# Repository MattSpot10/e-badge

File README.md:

# eBadge

**eBadge** is a customizable, hackable electronics badge designed for students to explore, build, and learn throughout their academic journey. It’s more than just a badge—it's a personal electronics lab, wearable project canvas, and long-term learning tool.

## Features

- Custom PCB with microcontroller 
- Modular peripherals: LEDs, sensors, buttons, displays, etc.
- Fully programmable with open-source firmware
- Designed for learning — from blinking LEDs to building full apps
- Battery-powered & portable — perfect for hacking on the go

## What’s in This Repo?

```bash
e-badge/
├── docs/           # Project documentation, setup guides, and images
├── hardware/       # Schematics, PCB layouts, BOMs, and 3D models
├── firmware/       # Embedded code for the badge's microcontroller
├── software/       # Host-side apps, test tools, or configurators
├── assets/         # Logos, badge graphics, and artwork
├── test/           # Scripts for testing hardware and firmware
├── LICENSE-CODE
├── LICENSE-HARDWARE
├── LICENSE-DOCS
├── README.md
└── .gitignore
```
## License

- **Hardware** – [CERN-OHL-S v2.0](./LICENSE-HARDWARE)
- **Firmware/Code** – [MIT License](./LICENSE-CODE)
- **Docs & Assets** – [CC BY-SA 4.0](./LICENSE-DOCS)

## Contributors

- Nathan Jack (jackn@byui.edu)
- Lynn Watson (watsonl@byui.edu)
- Jason Allred (allredjas@byui.edu)
- Richard Grimmett (grimmettr@byui.edu)
- Carl Gibbons (gibbonsc@byui.edu)
- Craig Lindstrom (lindstromc@byui.edu)
- Gary Godderidge (godderidgeg@byui.edu)
- Matt Manley (manleym@byui.edu)

# TODO (Senior project, delete when done)
- Fix screen connector
	- Use LCSC part C11086

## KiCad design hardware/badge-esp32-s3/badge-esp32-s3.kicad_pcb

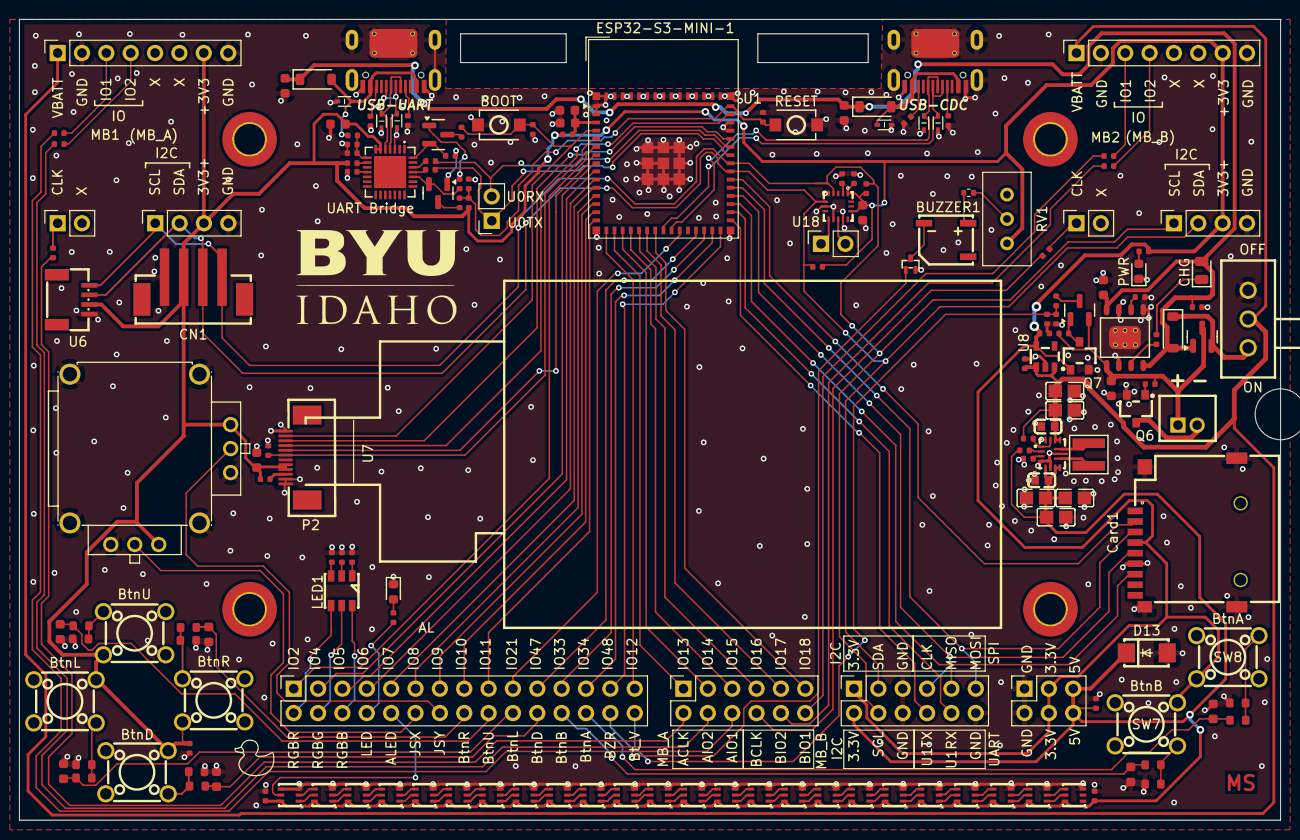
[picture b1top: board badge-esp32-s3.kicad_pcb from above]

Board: 2 copper layers, 131.5 x 83.5 mm, 180 parts (0 on the bottom side), 169 nets.

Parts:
AL1, AL2, AL3, AL4, AL5, AL6, AL7, AL8, AL9, AL10, AL11, AL12, AL13, AL14, AL15, AL16, AL17, AL18, AL19, AL20, AL21, AL22, AL23, AL24: LED-SMD_6P-L2.2-W2.2-TL-1
BUZZER1: MLT-5020; BUZ-SMD_L5.0-W5.5-P4.60
C1, C5, C6, C7, C12, C13: 10uF; C_0603
C2, C14: 100nF; C_0603
C3, C4, C8, C9, C15, C16, C32, C33: 1uF; C_0402
C10, C11, C25, C34, C35, C36: 100nF; C_0402
C17, C27: 10uF; C0805
C18, C19, C20, C21, C22, C23: 1uF; C_0603
C26: 4.7uF; C_0603
C28, C37: TMK107BBJ106MA-T; C0603
C29, C30, C31: 22uF; C0805
CN1: B4B-PH-SM4-TB (LF)(SN); CONN-SMD_B4B-PH-SM4-TB-LF-SN
Card1: TF PUSH; TF-SMD_TF-PUSH
D1, D14: Red; D_0603
D2, D3, D4, D6, D7, D8: LESD5D5.0CT1G; SOD-523_L1.2-W0.8-LS1.6-BI
D5, D9, D11: B0520W; D_SOD-123
D12: Green; D_0805
D13: SMAJ7.0A; SMA_L4.5-W2.6-LS5.1-RD
H1, H2, H3, H4: MountingHole; MountingHole_3.2mm_M3_ISO7380_Pad_TopBottom
H5: MountingHole; MountingHole_5.3mm_M5
J1, J2: Connector, USB-TYPE-C-16P; TYPE-C-SMD_HX-TYPE-C-16PIN
J3, J9: Conn_02x06_Odd_Even; PinSocket_2x06_P2.54mm_Vertical
J4: Conn_02x15_Odd_Even; PinSocket_2x15_P2.54mm_Vertical
J5, J12, J14, J15: Conn_01x02_Socket; PinSocket_1x02_P2.54mm_Vertical
J6, J13: Conn_01x04_Socket; PinSocket_1x04_P2.54mm_Vertical
J7, J8: Conn_01x08_Socket; PinSocket_1x08_P2.54mm_Vertical
J11: Conn_02x03_Odd_Even; PinSocket_2x03_P2.54mm_Vertical
L3: XGL4020-152MEC; IND-SMD_L4.0-W4.0_XEL4020
LED1: RS-3535MWAM; LED-ARRAY-SMD_L3.7-W3.5-P1.10-TL
MB1, MB2: MiniBadge_Full; MiniBadge_Full_NoEdges
P1: PH-2A_C2319; CONN-TH_2P-P2.00_PH-2A_C2319
P2: FPC 0.5MM 12P Pull type H2.0mm Pick up; FPC-SMD_12P-L11.5-W5.4-P0.50
Power1: SK-12F04-G050; SW-TH_G-SWITCH_SK-12F04-G050
Q1, Q2: SS8050 200-350; Q_SOT-23
Q3, Q4: HL2301A; Q_SOT-23
Q5: DTC114E; DTC114EE
Q6, Q7: AO3424; SC-59-3_L2.9-W1.6-P0.95-LS2.9-BR
R1, R11, R12: 0Ω; R_0402
R2, R3, R4, R5, R6, R19: 5.1kΩ; R_0402
R7: 22kΩ; R_0402
R8, R46: 47kΩ; R_0402
R9, R25: 1kΩ; R_0402
R10, R13, R14, R17, R54: 10kΩ; R_0402
R15, R16: 470Ω; R_0402
R18, R20, R40, R47, R49, R50, R51, R52: 100Ω; R_0402
R21, R22: 47Ω; R_0402
R23: YF16-FL7.2-B5KA(45-10)-R-A28; JOYTICK-TH_YF16-DFL7.2-B5KO-45-10-B5KO-55--RG-A22
R24, R39, R44, R48, R53: 100kΩ; R_0402
R26: 2.2kΩ; R_0402
R27, R28, R29, R30, R31, R32, R33, R34, R35, R36, R37, R38: 10kΩ; R_0603
R41: 150kΩ; R_0402
R42: 27Ω; R_0402_1005Metric
R43, R45: 4.7kΩ; R_0402
RV1: 1000Ω; Potentiometer_Bourns_3296W_Vertical
SW1, SW2: TS-1088-AR02016; SW-SMD_L3.9-W3.0-P4.45
SW4, SW5, SW6, SW7, SW8, SW9: TS665CJ; SW-TH_4P-L6.0-W6.0-P4.50-LS6.5
U1: ESP32-S3-MINI-1-N4R2; ESP32-S2-MINI-1
U2: TPS630701RNMR; VQFN-HR-15_L3.0-W2.5-P0.50-BL_TPS63070RNMR
U3: CP2102N-A02-GQFN28R; QFN-28_L5.0-W5.0-P0.50-TL-EP3.3
U4: TP4056; ESOP-8_L4.9-W3.9-P1.27-LS6.0-BL-EP
U6: ZX-SH1.0-4PWT; CONN-SMD_4P-P1.00_MEGASTAR_ZX-SH1.0-4PWT
U7: HS20HS072RX-fpc; OLED-SMD_HS20HS072RX-pins_removed
U8: TLV75733PDBVR; SOT-23-5_L2.9-W1.6-P0.95-LS2.8-BL
U18: MMA8452QR1_C11360; QFN-16_L3.0-W3.0-P0.50-TL_MMA8452QR1

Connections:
+3.3V: C4.1, C7.1, C10.1, C14.1, C16.1, C26.2, CN1.3, Card1.4 (VDD), J3.1, J6.3, J7.7, J8.7, J11.3, J11.4, J13.3, P2.8 (IOVCC), P2.9 (VCC), Q7.1 (G), R1.2, R2.1, R9.2, R17.1, R18.1, R23.3, R23.4, R43.1, R45.1, RV1.1, SW4.2 (B), SW5.2 (B), SW6.2 (B), SW7.2 (B), SW8.2 (B), SW9.2 (B), U3.6 (VDD), U3.7 (VREGIN), U6.3, U8.5 (OUT), U18.1 (VDDIO), U18.14 (VDD)
/5V_stable: AL1.3 (VDD), AL2.3 (VDD), AL3.3 (VDD), AL4.3 (VDD), AL5.3 (VDD), AL6.3 (VDD), AL7.3 (VDD), AL8.3 (VDD), AL9.3 (VDD), AL10.3 (VDD), AL11.3 (VDD), AL12.3 (VDD), AL13.3 (VDD), AL14.3 (VDD), AL15.3 (VDD), AL16.3 (VDD), AL17.3 (VDD), AL18.3 (VDD), AL19.3 (VDD), AL20.3 (VDD), AL21.3 (VDD), AL22.3 (VDD), AL23.3 (VDD), AL24.3 (VDD), C15.1, C29.2, C30.2, C31.2, C32.1, C33.1, C37.2, D13.1 (K), J3.2, J11.5, J11.6, R53.1, U2.5 (FB), U2.7 (VOUT), U2.8 (VOUT)
/AButtonMid: C22.1, J4.26, R36.2
/AddrLedMid: AL1.2 (DI), J4.10
/BButtonMid: C21.1, J4.24, R34.2
/BatteryVoltage: C34.1, J4.30, R41.2, R46.1
/BuzzerMid: J4.28, Q5.1 (B)
/DownButtonMid: C23.1, J4.22, R38.2
/ESP_EN: C9.1, C36.2, R15.2, R17.2, SW2.2, U1.45 (EN)
/ESP_USB+: D6.2, J2.A6 (D+), J2.B6 (D+), U1.24 (USB_D+)
/ESP_USB-: D7.2, J2.A7 (D-), J2.B7 (D-), U1.23 (USB_D-)
/GPIO0: C35.2, P2.2 (CS), R16.2, SW1.2, U1.4 (IO0)
/GPIO1: P2.6 (RST), R39.1, U1.5 (IO1)
/GPIO2: J4.1, U1.6 (IO2)
/GPIO3: P2.5 (SDA), U1.7 (IO3)
/GPIO4: J4.3, U1.8 (IO4)
/GPIO5: J4.5, U1.9 (IO5)
/GPIO6: J4.7, U1.10 (IO6)
/GPIO7: J4.9, U1.11 (IO7)
/GPIO8: J4.11, U1.12 (IO8)
/GPIO9: J4.13, U1.13 (IO9)
/GPIO10: J4.15, U1.14 (IO10)
/GPIO11: J4.17, U1.15 (IO11)
/GPIO12: J4.29, U1.16 (IO12)
/GPIO13: J9.1, U1.17 (IO13)
/GPIO14: J9.3, U1.18 (IO14)
/GPIO15: J9.5, U1.19 (IO15)
/GPIO16: J9.7, U1.20 (IO16)
/GPIO17: J9.9, U1.21 (IO17)
/GPIO18: J9.11, U1.22 (IO18)
/GPIO21: J4.19, U1.25 (IO21)
/GPIO33: J4.23, U1.28 (IO33)
/GPIO34: J4.25, U1.29 (IO34)
/GPIO35: J3.8, U1.31 (IO35)
/GPIO36: J3.10, U1.32 (IO36)
/GPIO37: Card1.7 (DAT0), J3.9, U1.33 (IO37)
/GPIO38: Card1.5 (CLX), J3.7, U1.34 (IO38)
/GPIO39: Card1.3 (CMD), J3.11, U1.35 (IO39)
/GPIO40: Card1.2 (CD/DAT3), U1.36 (IO40)
/GPIO41: CN1.2, J3.3, J6.2, J13.2, R45.2, U1.37 (IO41), U6.2, U18.6 (SDA)
/GPIO42: CN1.1, J3.4, J6.1, J13.1, R43.2, U1.38 (IO42), U6.1, U18.4 (SCL)
/GPIO45: P2.3 (RS), U1.41 (IO45)
/GPIO46: P2.4 (SCL), U1.44 (IO46)
/GPIO47: J4.21, U1.27 (IO47)
/GPIO48: J4.27, U1.30 (IO48)
/JoystickXMid: J4.12, R23.2
/JoystickYMid: J4.14, R23.5
/LEDSingleMid: J4.8, R19.1
/LEDs/BO_AL9: AL9.5 (BO), AL10.1 (BI)
/LEDs/BO_AL18: AL18.5 (BO), AL19.1 (BI)
/LEDs/DO_AL9: AL9.4 (DO), AL10.2 (DI)
/LEDs/DO_AL18: AL18.4 (DO), AL19.2 (DI)
/LeftButtonMid: C18.1, J4.20, R28.2
/Onboard Peripheral/Accelormeter/INT 1 (output to MCU, NN): J15.2, U18.11 (INT1)
/Onboard Peripheral/Accelormeter/INT 2 (output to MCU, NN): J15.1, U18.9 (INT2)
/RGBBlueMid: J4.6, LED1.6 (+)
/RGBGreenMid: J4.4, LED1.5 (+)
/RGBRedMid: J4.2, LED1.4 (+)
/RightButtonMid: C20.1, J4.16, R32.2
/U0RX: J14.2, R11.2, U1.40 (RXD0)
/U0TX: J14.1, R12.2, U1.39 (TXD0)
/UART Interface/USB_DN: D3.2, J1.A7 (D-), J1.B7 (D-), U3.5 (D-)
/UART Interface/USB_DP: D2.2, J1.A6 (D+), J1.B6 (D+), U3.4 (D+)
/USB_5V: C5.1, C6.1, C12.1, D5.1, D9.1, D11.2, D12.2, Q3.1 (G), R24.2, U4.4 (VCC), U4.8 (CE)
/UpButtonMid: C19.1, J4.18, R30.2
/VBATT: C13.1, P1.1, Q3.3 (D), Q4.2 (S), R44.1, R48.2, U4.5 (BAT)
/VBUS: D4.2, D5.2, J1.A9B4 (VBUS), J1.B9A4 (VBUS), R7.1
/VBUSB: D8.2, D9.2, J2.A9B4 (VBUS), J2.B9A4 (VBUS)
/minibadge/MB1CLK: J9.2, R49.2
/minibadge/MB1IO1: J9.6, R40.1
/minibadge/MB1IO2: J9.4, R47.1
/minibadge/MB2CLK: J9.8, R52.2
/minibadge/MB2IO1: J9.12, R50.1
/minibadge/MB2IO2: J9.10, R51.1
GND: AL1.1 (BI), AL1.6 (GND), AL2.6 (GND), AL3.6 (GND), AL4.6 (GND), AL5.6 (GND), AL6.6 (GND), AL7.6 (GND), AL8.6 (GND), AL9.6 (GND), AL10.6 (GND), AL11.6 (GND), AL12.6 (GND), AL13.6 (GND), AL14.6 (GND), AL15.6 (GND), AL16.6 (GND), AL17.6 (GND), AL18.6 (GND), AL19.6 (GND), AL20.6 (GND), AL21.6 (GND), AL22.6 (GND), AL23.6 (GND), AL24.6 (GND), C1.2, C2.2, C3.2, C4.2, C5.2, C6.2, C7.2, C8.2, C9.2, C10.2, C11.2, C12.2, C13.2, C14.2, C15.2, C16.2, C17.1, C18.2, C19.2, C20.2, C21.2, C22.2, C23.2, C25.2, C26.1, C27.1, C28.1, C29.1, C30.1, C31.1, C32.2, C33.2, C34.2, C35.1, C36.1, C37.1, CN1.4, Card1.6 (VSS), Card1.10, Card1.11, Card1.12, Card1.13, D1.1, D2.1, D3.1, D4.1, D6.1, D7.1, D8.1, D13.2 (A), D14.1, J1.A12B1 (GND), J1.B12A1 (GND), J1.S1 (SHIELD), J2.A12B1 (GND), J2.B12A1 (GND), J2.S1 (SHIELD), J3.5, J3.6, J3.12, J6.4, J7.2, J7.8, J8.2, J8.8, J11.1, J11.2, J13.4, P2.1 (GND), P2.11 (K), P2.12 (GND), Power1.3, Q5.2 (E), Q6.2 (S), Q7.2 (S), R3.2, R4.2, R5.2, R6.2, R8.2, R10.2, R20.2, R21.2, R22.2, R23.1, R23.6, R23.7 (shell), R23.8 (shell), R23.9 (shell), R23.10 (shell), R24.1, R26.2, R27.2, R29.2, R31.2, R33.2, R35.2, R37.2, R39.2, R46.2, SW1.1, SW2.1, U1.1 (GND), U1.2 (GND), U1.42 (GND), U1.43 (GND), U1.46 (GND), U1.47 (GND), U1.48 (GND), U1.49 (GND), U1.50 (GND), U1.51 (GND), U1.52 (GND), U1.53 (GND), U1.54 (GND), U1.55 (GND), U1.56 (GND), U1.57 (GND), U1.58 (GND), U1.59 (GND), U1.60 (GND), U1.61 (GND), U1.62 (GND), U1.63 (GND), U1.64 (GND), U1.65 (GND), U2.4 (GND), U2.6 (FB2), U2.10 (PGND), U2.15 (VSEL), U3.3 (GND), U4.1 (TEMP), U4.3 (GND), U4.6 (STDBY#), U4.9 (EP), U6.4, U8.2 (GND), U18.5 (GND), U18.7 (SA0), U18.10 (GND), U18.12 (GND)
unnamed: AL1.5 (BO), AL2.1 (BI)
unnamed: AL1.4 (DO), AL2.2 (DI)
unnamed: AL2.5 (BO), AL3.1 (BI)
unnamed: AL2.4 (DO), AL3.2 (DI)
unnamed: AL3.5 (BO), AL4.1 (BI)
unnamed: AL3.4 (DO), AL4.2 (DI)
unnamed: AL4.5 (BO), AL5.1 (BI)
unnamed: AL4.4 (DO), AL5.2 (DI)
unnamed: AL5.5 (BO), AL6.1 (BI)
unnamed: AL5.4 (DO), AL6.2 (DI)
unnamed: AL6.5 (BO), AL7.1 (BI)
unnamed: AL6.4 (DO), AL7.2 (DI)
unnamed: AL7.5 (BO), AL8.1 (BI)
unnamed: AL7.4 (DO), AL8.2 (DI)
unnamed: AL8.5 (BO), AL9.1 (BI)
unnamed: AL8.4 (DO), AL9.2 (DI)
unnamed: AL10.5 (BO), AL11.1 (BI)
unnamed: AL10.4 (DO), AL11.2 (DI)
unnamed: AL11.5 (BO), AL12.1 (BI)
unnamed: AL11.4 (DO), AL12.2 (DI)
unnamed: AL12.5 (BO), AL13.1 (BI)
unnamed: AL12.4 (DO), AL13.2 (DI)
unnamed: AL13.5 (BO), AL14.1 (BI)
unnamed: AL13.4 (DO), AL14.2 (DI)
unnamed: AL14.5 (BO), AL15.1 (BI)
unnamed: AL14.4 (DO), AL15.2 (DI)
unnamed: AL15.5 (BO), AL16.1 (BI)
unnamed: AL15.4 (DO), AL16.2 (DI)
unnamed: AL16.5 (BO), AL17.1 (BI)
unnamed: AL16.4 (DO), AL17.2 (DI)
unnamed: AL17.5 (BO), AL18.1 (BI)
unnamed: AL17.4 (DO), AL18.2 (DI)
unnamed: AL19.5 (BO), AL20.1 (BI)
unnamed: AL19.4 (DO), AL20.2 (DI)
unnamed: AL20.5 (BO), AL21.1 (BI)
unnamed: AL20.4 (DO), AL21.2 (DI)
unnamed: AL21.5 (BO), AL22.1 (BI)
unnamed: AL21.4 (DO), AL22.2 (DI)
unnamed: AL22.5 (BO), AL23.1 (BI)
unnamed: AL22.4 (DO), AL23.2 (DI)
unnamed: AL23.5 (BO), AL24.1 (BI)
unnamed: AL23.4 (DO), AL24.2 (DI)
unnamed: BUZZER1.1 (+), R42.2
unnamed: BUZZER1.2 (-), Q5.3 (C)
unnamed: D1.2, R2.2
unnamed: D12.1, R25.1
unnamed: D14.2, R19.2
unnamed: J1.A5 (CC1), R3.1
unnamed: J1.B5 (CC2), R4.1
unnamed: J2.A5 (CC1), R5.1
unnamed: J2.B5 (CC2), R6.1
unnamed: J5.1, R49.1
unnamed: J7.3, R40.2
unnamed: J7.4, R47.2
unnamed: J8.3, R50.2
unnamed: J8.4, R51.2
unnamed: J12.1, R52.1
unnamed: LED1.1 (-), R21.1
unnamed: LED1.2 (-), R22.1
unnamed: LED1.3 (-), R20.1
unnamed: P2.10 (A), R18.2
unnamed: Q1.1 (B), R13.2
unnamed: Q1.3 (C), R15.1
unnamed: Q1.2 (E), R14.1, U3.24 (RTS)
unnamed: Q2.1 (B), R14.2
unnamed: Q2.3 (C), R16.1
unnamed: Q2.2 (E), R13.1, U3.28 (DTR)
unnamed: D11.1, Power1.1, Q3.2 (S)
unnamed: Q4.3 (D), R41.1
unnamed: Q4.1 (G), Q7.3 (D), R44.2
unnamed: P1.2, Q6.3 (D)
unnamed: Q6.1 (G), R48.1
unnamed: R42.1, RV1.2
unnamed: R27.1, R28.1, SW4.4 (D)
unnamed: R29.1, R30.1, SW5.4 (D)
unnamed: R31.1, R32.1, SW6.4 (D)
unnamed: R33.1, R34.1, SW7.4 (D)
unnamed: R35.1, R36.1, SW8.3 (C)
unnamed: R37.1, R38.1, SW9.4 (D)
unnamed: C1.1, C2.1, R1.1, U1.3 (3V3)
unnamed: R54.2, U2.1 (PS/SYNC), U2.14 (EN)
unnamed: L3.1, U2.11 (L1)
unnamed: L3.2, U2.9 (L2)
unnamed: R53.2, U2.2 (PG)
unnamed: C25.1, U2.3 (VAUX)
unnamed: R9.1, U3.9 (RSTb)
unnamed: R12.1, U3.25 (RXD)
unnamed: R10.1, U3.11 (SUSPENDb)
unnamed: R11.1, U3.26 (TXD)
unnamed: C8.1, R7.2, R8.1, U3.8 (VBUS)
unnamed: R25.2, U4.7 (CHRG#)
unnamed: R26.1, U4.2 (PROG)
unnamed: C11.1, U18.2 (BYP)
PWR_RAW: C3.1, C17.2, C27.2, C28.2, J7.1, J8.1, Power1.2, R54.1, U2.12 (VIN), U2.13 (VIN), U8.1 (IN), U8.3 (EN)

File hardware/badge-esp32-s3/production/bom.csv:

Designator,Footprint,Quantity,Value,LCSC Part #
"AL1, AL10, AL11, AL12, AL13, AL14, AL15, AL16, AL17, AL18, AL19, AL2, AL20, AL21, AL22, AL23, AL24, AL3, AL4, AL5, AL6, AL7, AL8, AL9",LED-SMD_6P-L2.2-W2.2-TL-1,24,~,C22371528
BUZZER1,BUZ-SMD_L5.0-W5.5-P4.60,1,MLT-5020,C94598
"C1, C12, C13, C5, C6, C7",C_0603,6,10uF,C96446
"C10, C11, C24, C34, C35, C36",C_0402,6,100nF,C1525
"C14, C2",C_0603,2,100nF,C14663
"C15, C16, C3, C32, C33, C4, C8, C9",C_0402,8,1uF,C52923
"C17, C27",C0805,2,10uF,
"C18, C19, C20, C21, C22, C23",C_0603,6,1uF,C15849
C26,C_0603,1,4.7uF,C19666
"C29, C30, C31",C0805,3,22uF,
CARD1,TF-SMD_TF-PUSH,1,TF PUSH,C393941
CN1,CONN-SMD_B4B-PH-SM4-TB-LF-SN,1,B4B-PH-SM4-TB (LF)(SN),C160354
"D1, D14",D_0603,2,Red,C2286
"D11, D5, D9",D_SOD-123,3,B0520W,C7502707
D12,D_0805,1,Green,C2297
D13,SMA_L4.5-W2.6-LS5.1-RD,1,SMAJ7.0A,
"D2, D3, D4, D6, D7, D8",SOD-523_L1.2-W0.8-LS1.6-BI,6,LESD5D5.0CT1G,C5199850
"J1, J2",TYPE-C-SMD_HX-TYPE-C-16PIN,2,"Connector, USB-TYPE-C-16P",C2927039
J11,PinSocket_2x03_P2.54mm_Vertical,1,Conn_02x03_Odd_Even,C541853
"J12, J14, J15, J5",PinSocket_1x02_P2.54mm_Vertical,4,Conn_01x02_Socket,C7499322
"J13, J6",PinSocket_1x04_P2.54mm_Vertical,2,Conn_01x04_Socket,C2718488
"J3, J9",PinSocket_2x06_P2.54mm_Vertical,2,Conn_02x06_Odd_Even,C5307342
J4,PinSocket_2x15_P2.54mm_Vertical,1,Conn_02x15_Odd_Even,C7499350
"J7, J8",PinSocket_1x08_P2.54mm_Vertical,2,Conn_01x08_Socket,C42385698
L1,IND-SMD_L4.0-W4.0_XFL4020-102MEB,1,1uH,C5355380
LED1,LED-ARRAY-SMD_L3.7-W3.5-P1.10-TL,1,RS-3535MWAM,C842778
P1,CONN-TH_2P-P2.00_PH-2A_C2319,1,PH-2A_C2319,C2319
P2,FPC-SMD_12P-L11.5-W5.4-P0.50,1,FPC 0.5MM 12P Pull type H2.0mm Pick up,C11086
POWER1,SW-TH_G-SWITCH_SK-12F04-G050,1,SK-12F04-G050,C2848876
"Q1, Q2",Q_SOT-23,2,SS8050 200-350,C2150
"Q3, Q4",Q_SOT-23,2,HL2301A,C7420344
Q5,DTC114EE,1,DTC114E,C94400
"Q6, Q7",SC-59-3_L2.9-W1.6-P0.95-LS2.9-BR,2,AO3424,C475606
"R1, R11, R12",R_0402,3,0Ω,C17168
"R10, R13, R14, R17",R_0402,4,10kΩ,C25744
"R15, R16",R_0402,2,470Ω,C25117
"R18, R20, R40, R47, R49, R50, R51, R52",R_0402,8,100Ω,C25076
"R19, R2, R3, R4, R5, R6",R_0402,6,5.1kΩ,C25905
"R21, R22",R_0402,2,47Ω,C25118
R23,JOYTICK-TH_YF16-DFL7.2-B5KO-45-10-B5KO-55--RG-A22,1,YF16-FL7.2-B5KA(45-10)-R-A28,C37323739
"R24, R39, R44, R48",R_0402,4,100kΩ,C25741
"R25, R9",R_0402,2,1kΩ,C11702
R26,R_0402,1,2.2kΩ,C25879
"R27, R28, R29, R30, R31, R32, R33, R34, R35, R36, R37, R38",R_0603,12,10kΩ,C25804
R41,R_0402,1,150kΩ,C25755
R42,0402,1,27Ω,
"R43, R45",R_0402,2,4.7kΩ,C25900
"R46, R8",R_0402,2,47kΩ,C25792
R7,R_0402,1,22kΩ,C25768
RV1,Potentiometer_Bourns_3296W_Vertical,1,1000Ω,C57089
"SW1, SW2",SW-SMD_L3.9-W3.0-P4.45,2,TS-1088-AR02016,C720477
"SW4, SW5, SW6, SW7, SW8, SW9",SW-TH_4P-L6.0-W6.0-P4.50-LS6.5,6,TS665CJ,C393938
U1,ESP32-S2-MINI-1,1,ESP32-S3-MINI-1-N4R2,C3013941
U18,QFN-16_L3.0-W3.0-P0.50-TL_MMA8452QR1,1,MMA8452QR1_C11360,C11360
U3,QFN-28_L5.0-W5.0-P0.50-TL-EP3.3,1,CP2102N-A02-GQFN28R,C964632
U4,ESOP-8_L4.9-W3.9-P1.27-LS6.0-BL-EP,1,TP4056,C16581
U5,WSON-10_L3.0-W3.0-P0.50-BL-EP-A,1,TPS63061DSCR,
U6,CONN-SMD_4P-P1.00_MEGASTAR_ZX-SH1.0-4PWT,1,ZX-SH1.0-4PWT,C7430446
U7,OLED-SMD_HS20HS072RX-pins_removed,1,HS20HS072RX-fpc,C5329582
U8,SOT-23-5_L2.9-W1.6-P0.95-LS2.8-BL,1,TLV75733PDBVR,C485517

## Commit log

2025-06-16 Add micro SD slot LCSC part
2025-06-17 Add button to library
2025-06-17 Add JST PH 4 pin part to library
2025-06-17 Add JST SH 4 pin part to library
2025-06-18 Fixed Button, Added Joystick
    Button's extra resistor was removed
    Buttons were added to Onboard Peripheral sub sheet (all 6)
    Joystick was added to library + onboard Peripheral sub sheet in its own sub sheet.
2025-06-18 Added filter capacitor, upped PD to 100k, Removed 2 unused sheets
    Added a 100nF filter capacitor in parallel with the PD resistor (now 100k)
    Removed PushButton and PushButtonPB(a typo) subsheets as they are unused.
2025-06-18 JST PH and JST SH headers completed
    Both subsheets are in exposed pins subsheet. I also had to make the symbols and footprints associated with each other.
2025-06-19 Resistor Fix
    PD resistor 100k -> 47k
2025-06-20 Fully swap from WROOM to MINI MCU package
2025-06-21 Add parts requested by Everett and Getu
2025-06-21 Add parts from branches that are causing conflicts Library updates should have linear history in the future
2025-06-24 Accelerometer
    I Ended up doing just the accelerometer, the others would have taken more pins etc.
2025-06-24 Updated PD schematic
    Changed the button debounce schematic.
2025-06-24 Update badge-esp32-s3.kicad_sch
    GPIO pins labeled
2025-06-24 GPIO pins labeled
    GPIO pins labeled on the MCU
2025-06-24 PD updated once again
2025-06-24 Add buzzer
2025-06-24 Add new tri-color LED, library update
2025-06-25 Switch on LDO enable pin
2025-06-25 Revert "Merge branch 'main' into Danny"
    This reverts commit f39a0d75d6025751b3d0be32cc251741b689ee9f, reversing
    changes made to 38c8f4414de6e086c66d277d9ce522e64904a3dc.
2025-06-25 GPIO connections made (USB and External Pins yet to be done)
2025-06-25 Make sure joystick gets 3.3V power
2025-06-25 Spelling error correction
2025-06-25 Add edge cuts The reference designators need to updated in the schematic
2025-06-25 Reapply "Merge branch 'main' into Danny"
    This reverts commit 522ccfdb580e54901b8ff562dc2e90cfc327c6b7.
2025-06-25 Moved Switch posistion
2025-06-26 Fem_headers
    Fem headers done
2025-06-26 add 3v3 to minibadge
2025-06-26 Fix lcsc symbol library not working
2025-06-26 Fleshed out schematic with all exposed pins
2025-06-26 Library update
2025-06-26 Annotate schematic
2025-06-26 Fix some DRC errors
2025-06-26 add minibadge 2.1b library
2025-06-26 Finish schematic, start placing parts on layout
2025-06-26 Moved header for exsample
    moved a component to show how to push to git
2025-06-26 Layout placed
    I've completed the PCB layout and am handing it off for trace routing. It's been a while since I last did this, so while I did my best to optimize placement, there may be areas where space is tight. 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
    Feedback is welcome—I wish I had more time to do the traces myself since that would be a valuable learning opportunit.
2025-06-27 Add nice silkscreens
2025-06-27 Start routing stuff Used free route, so it's not ideal
2025-06-27 errors and warnings resolved
    some warnings need to be addressed now and some errors are need to be rectified
2025-06-27 Fix additional DRC errors (5 left)
2025-06-27 Added Final Doc as MD for future editing
    Added Final Doc as MD for future editing
2025-06-27 First silkscreen version
2025-06-28 Finish beta layout for ordering
2025-06-28 Create Bill of Materials
    Needs some clarifying text, but good for now
2025-06-28 Create Hardware Datasheets
2025-06-28 This is a PDF of the schematic.
    We can make it prettier later. Gotten via the 'plot' function under file while in the schematic view of Kicad.
2025-07-09 Changed File name so its .md
2025-07-09 Removed DNP and Exclude categories for brevity
2025-07-09 Added labels data sheets, and moved data sheets to first item on table
2025-07-09 Updated Feature Requirements + added Known Issues,md in test folder
2025-07-10 Rename Hardware Datasheets to Hardware Datasheets.md
2025-07-10 Rename minibadge-links to minibadge-links.md
2025-07-10 Added buzzer and Joystick firmware tests
2025-07-10 Added Accelerometer and Screen Test
2025-07-11 Added firmware test
    Added two firmware test one that interfaces the buttons with the buzzer and one that shows different colors on the onboard RGB
2025-07-11 Updated Test Checklist
2025-07-11 Created the GPIO test
2025-07-15 Added BT scan
2025-07-16 created demo firmware
2025-07-16 SDcard Test
2025-09-10 Fix LCD connector
2025-09-26 Oopsies, forgot to push my changes for final production (Spring 2025)
2025-10-02 Update readme with LCD screen fix info
2025-10-02 Add comments in PCB editor EXTREMELY SEVERE DRC VIOLATIONS AFTER MERGING
2025-10-02 add connector with correct orientation for sceen
2025-10-06 Screen Port Fix
    Redo on the screen port fix on the most up-to-date board version.
2025-10-06 Created a documentation folder for documenting our changes and board versions.
2025-10-08 Updated the gitignore to exclude .lck files. Fixed the path to the misc-lib to be a relative path.
2025-10-08 GPIO Pin Swap
    Switch of GPIO pins so RGB LED is not on JTAG pins.
2025-10-08 joystick_fix
    I swapped the x and y contacts since they were reversed
2025-10-11 update labels for changes
2025-10-11 Updated the pin number to be CD on the sd_card.
2025-10-11 Updated the buzzer schematic and fixed the button traces.
2025-10-13 Updated the audio schematic and traces.
2025-10-16 Fixed nested git repo issue in backups
2025-10-16 Moved keypad and rerouted
2025-10-19 changes to labels
2025-10-19 minibadge fix
2025-10-19 Updated the PCB to have the gpio jumper pins.
2025-10-20 Update fp-info-cache
2025-10-20 Pin Change for RGB LED
    Updated RGB LED on root schematic to be up to date
    TODO: Update PCB
2025-10-20 minibadge on pcb
2025-10-22 minibadge changed to noedges
2025-10-23 footprint error fix
2025-10-23 RGB LED GPIO Pin Corrections
    Swapped GPIO header and RGB LED to accommodate new RGB LED GPIO pin locations.
    TODO: Rewire the GPIO header
2025-10-25 fix_SD_and_minibadge_pads
2025-10-25 more_fixes_and_routing
2025-10-25 fix_warnings_errors
2025-10-27 Worked on Resolving Ground Splitting
    See title.
    Further optimizations can be made.
2025-10-27 Consolidated the GPIO pins, communication pins, and power pins.
2025-10-27 Moved the addressable LEDs to the top.
2025-10-27 Swapped the RGB led pins.
2025-10-27 fix_sd_card_and_minibadge
2025-10-27 upload_fix_footprint
2025-10-27 Updated the buzzer to not use a jtag pin.
2025-10-28 Started routing the traces.
2025-10-29 Continued laying the traces.
2025-10-29 re_trace
2025-10-29 Updated the messed up labels.
2025-10-29 Updated the traces further.
2025-10-29 schematic_pwr
2025-10-29 Updated pins
    Updated pins and headers to avoid using internal flash SPI pins on schematic.
2025-10-29 pwr_fix
2025-10-29 delete_testing_pwr
2025-10-29 fix_label
2025-10-29 route
2025-10-30 Fixed the errors in the schematic, and redid some label
2025-10-31 Continued adding traces.
2025-10-31 finished routing the traces.
2025-10-31 Updated the exposed gpio block.
2025-10-31 rounting_add_holes_clean_errors
2025-11-01 Fixed the LCSC Part numbers.
2025-11-01 Updated pcb labels
2025-11-01 Updated the layout of a some of the traces.
2025-11-03 Updated Silkscreen
    Updated silkscreen on back of board to accommodate new pin mappings.
2025-11-03 Updated Pinout.md for e-Badge V3.0
    See title.
2025-11-05 Adding Tetris
    Adding both Arduino C and Micro Python versions of Tetris
2025-11-05 Made 5V pins that connect to the +4V line. That is the name of the net coming off of the power switch.
2025-11-06 minibadge_fix?
2025-11-06 unfinished_minibadge_fix
2025-11-06 Updated the wiring for the 5V line to be connected to the +4V net. That is what it is named even though it is 4.5 ish volts.
2025-11-08 changes_minibadge
2025-11-08 more_changes
2025-11-08 Started adding the circuitry for the 5V voltage booster.
2025-11-10 minibadge_fix_update
2025-11-10 Minibadge_final??
2025-11-10 Added capacitors and inductors for the buck boost converter.
2025-11-11 Added capacitors for the 5V booster circuit.
2025-11-12 Updated the ESP32 Chip to N4R2
2025-11-16 Added the buck-boost converter. The traces aren't all connected though.
2025-11-17 Update silkscreen
    Fixed BtnL and BtnR switch
    Changed silkscreen labels for buttons
2025-11-18 Add the ground plane for the 5V regulation circuit.
2025-11-20 Rotated U6, moved labels and renamed 3.3 to IO1
2025-11-20 rubber_duck
2025-11-22 moved the bar to be cented
2025-11-22 moved the bar to be better
2025-11-22 try again pls
2025-11-22 reverse_battery_pins_back
2025-11-22 Updated power label.
2025-11-22 reversed_labels_and_pcb
2025-11-22 Added boot and reset labels for buttons.
2025-11-22 Add Display Silkscreen
    See Summary
2025-11-22 I don't know what changed but I am pushing.
2025-11-22 Re-added the power switch label.
2025-11-22 rerouted the gpio pins
2025-11-22 Added thicker traces for the 5V circuit and added a TVS diode.
2025-11-23 routing_juan
2025-11-24 Update Silkscreen
    Corrected header pin names, added button names, repositioned back-of-board pinmapping, added updated QR-Code
2025-11-24 Readded Display Silkscreen
    See summary.
2025-11-24 More_routing
2025-11-24 Added thicker traces for the 5V line.
2025-11-24 Fixed the wiring for the 3.3V line.
2025-11-24 Swapped the diode direction.
2025-11-24 Updated switch label.
2025-11-24 Updated the TVS diode label.
2025-11-24 added boxes for spi and uart
2025-11-24 Updated labels for buttons
2025-11-24 updated version number
2025-11-24 ESP32-S3_mini-1-N4R2
2025-12-01 Added a datasheets folder.
2025-12-01 Added several datasheets.
2025-12-12 More datasheets
2025-12-12 printing docs
2025-12-15 Added a Test Code
2025-12-17 Removed the datasheets from github.
2026-01-27 changed joystick and fixed minibadge in the schematic
2026-02-01 added sdio
2026-02-25 almost finished
2026-02-25 final changes and part updated
2026-02-25 finished component alignment
2026-02-26 changed buck/boost reg and final touchups
2026-02-26 changed version to 4.0
